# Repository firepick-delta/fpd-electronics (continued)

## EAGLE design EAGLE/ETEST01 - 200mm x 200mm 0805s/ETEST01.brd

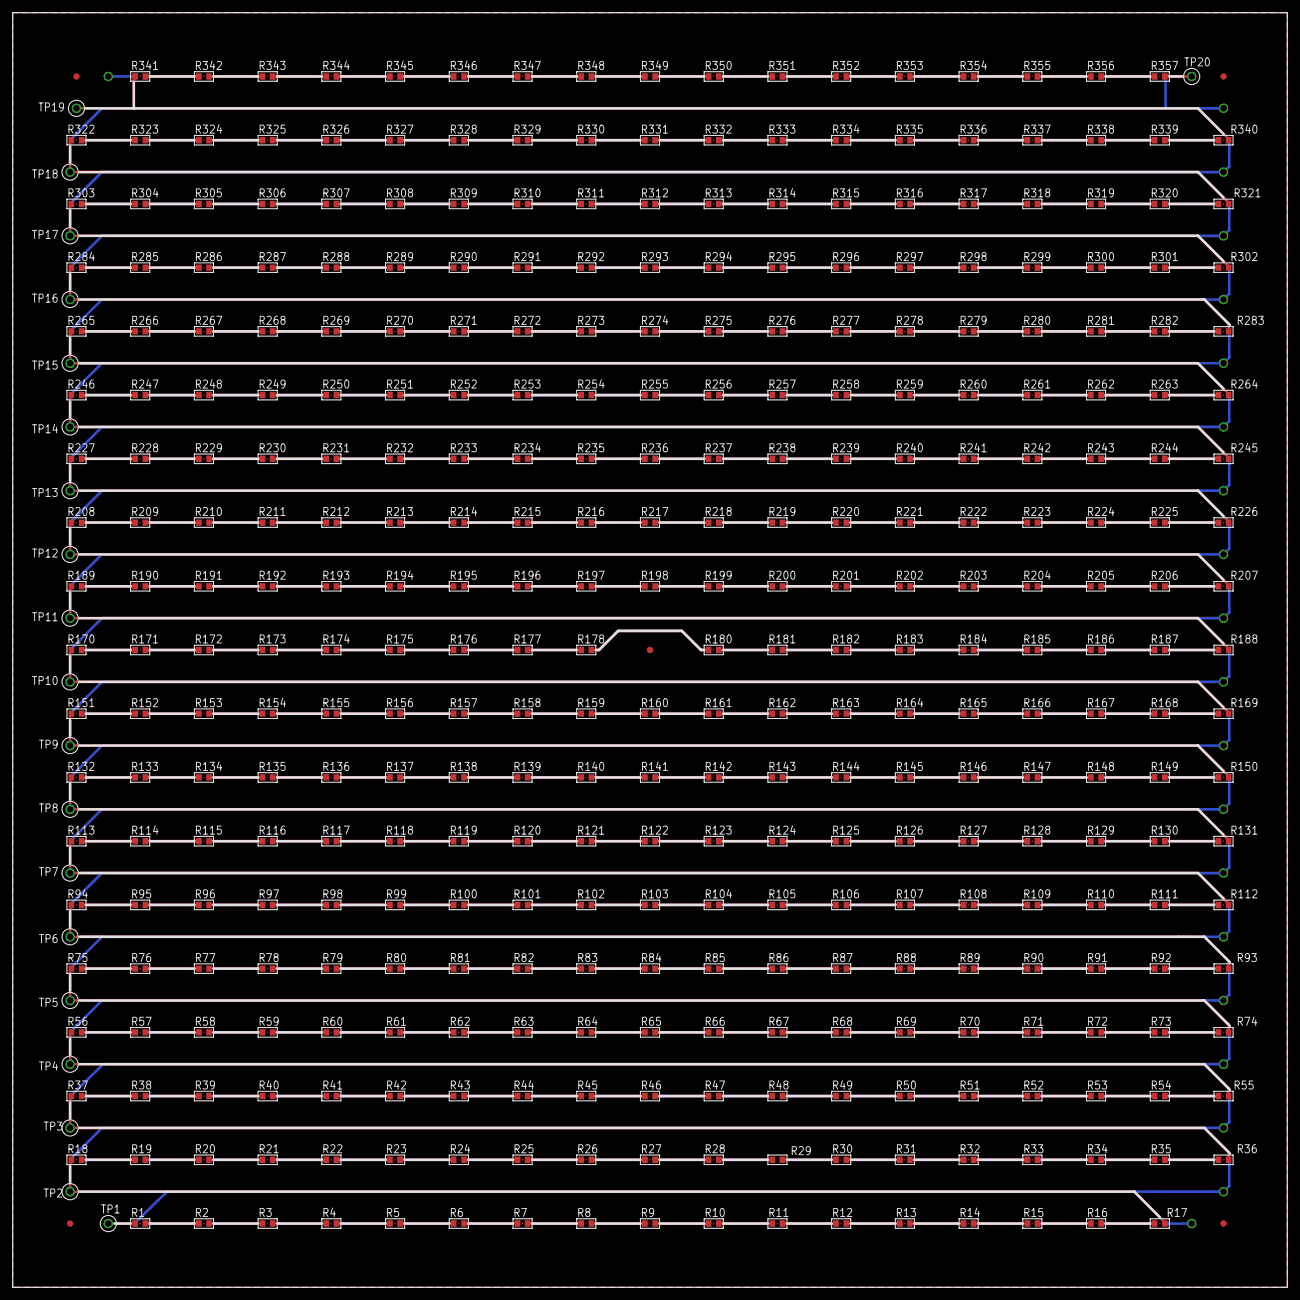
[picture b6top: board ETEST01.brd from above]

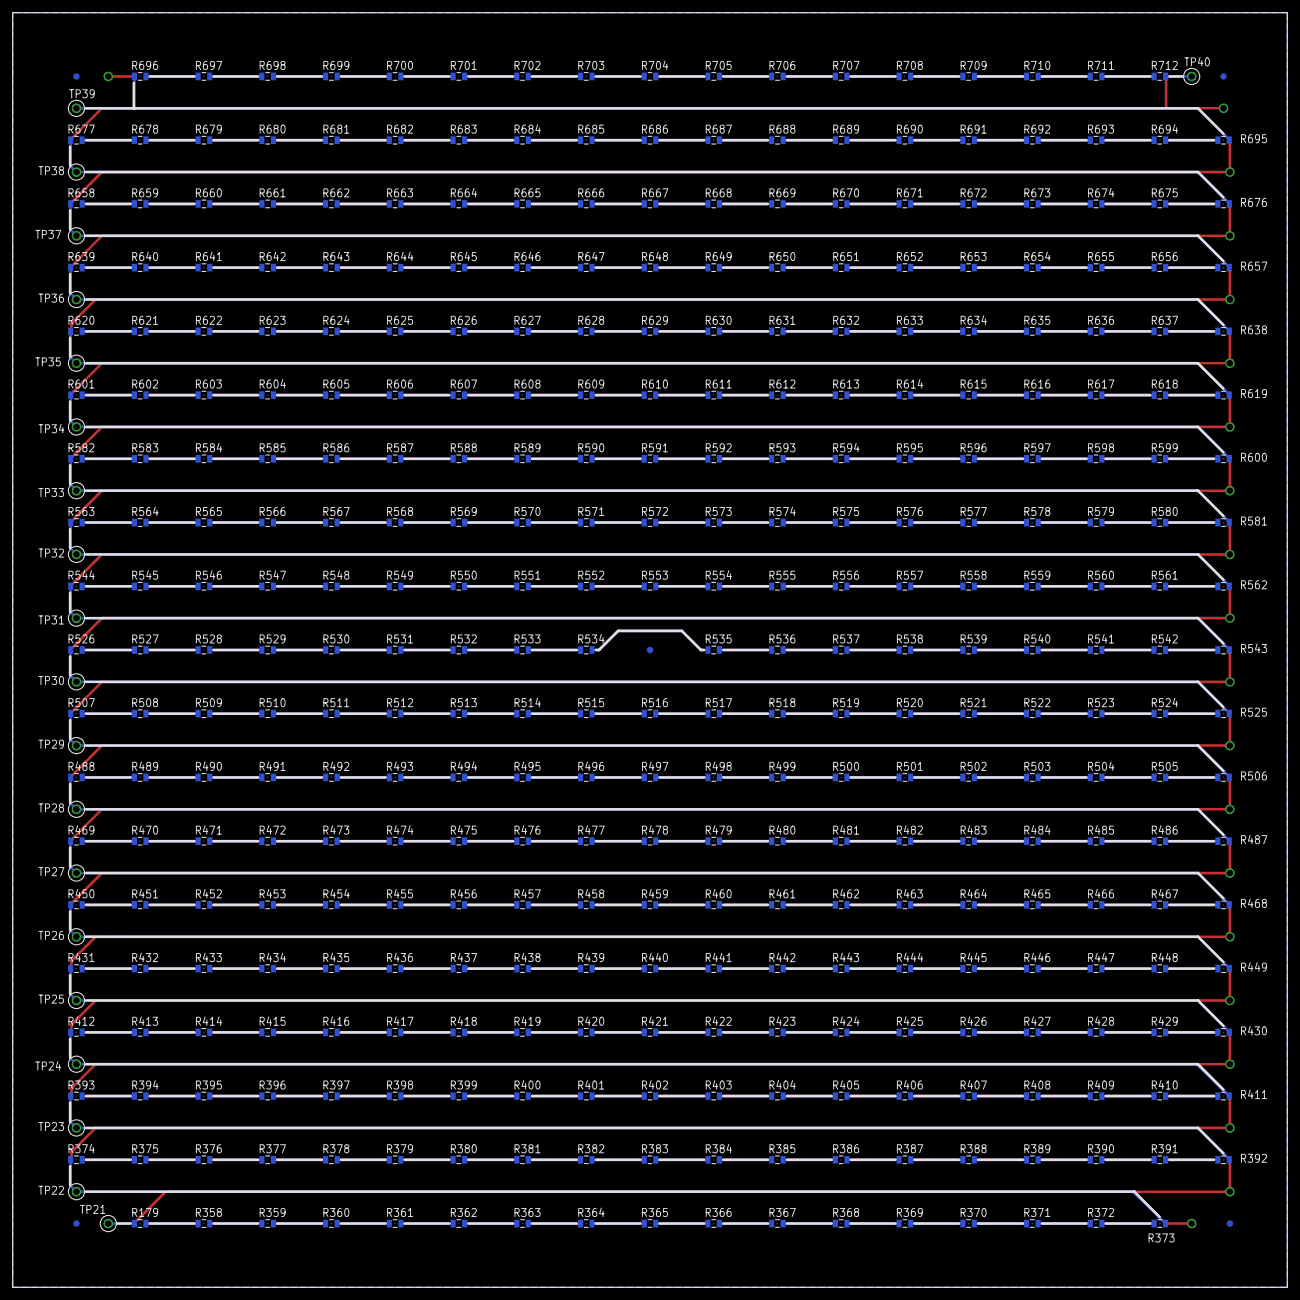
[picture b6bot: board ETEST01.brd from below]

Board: 2 copper layers, 200.0 x 200.0 mm, 762 parts (381 on the bottom side), 714 nets.

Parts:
FID1, FID2, FID3, FID4, FID5, FID6, FID7, FID8, FID9, FID10: FIDUCIAL
R1, R2, R3, R4, R5, R6, R7, R8, R9, R10, R11, R12, R13, R14, R15, R16, R17, R18, R19, R20, R21, R22, R23, R24, R25, R26, R27, R28, R30, R31, R32, R33, R34, R35, R36, R37, R38, R39, R40, R41, R42, R43, R44, R45, R46, R47, R48, R49, R50, R51, R52, R53, R54, R55, R56, R57, R58, R59, R60, R61, R62, R63, R64, R65, R66, R67, R68, R69, R70, R71, R72, R73, R74, R75, R76, R77, R78, R79, R80, R81, R82, R83, R84, R85, R86, R87, R88, R89, R90, R91, R92, R93, R94, R95, R96, R97, R98, R99, R100, R101, R102, R103, R104, R105, R106, R107, R108, R109, R110, R111, R112, R113, R114, R115, R116, R117, R118, R119, R120, R121, R122, R123, R124, R125, R126, R127, R128, R129, R130, R131, R132, R133, R134, R135, R136, R137, R138, R139, R140, R141, R142, R143, R144, R145, R146, R147, R148, R149, R150, R151, R152, R153, R154, R155, R156, R157, R158, R159, R160, R161, R162, R163, R164, R165, R166, R167, R168, R169, R170, R171, R172, R173, R174, R175, R176, R177, R178, R180, R181, R182, R183, R184, R185, R186, R187, R188, R189, R190, R191, R192, R193, R194, R195, R196, R197, R198, R199, R200, R201, R202, R203, R204, R205, R206, R207, R208, R209, R210, R211, R212, R213, R214, R215, R216, R217, R218, R219, R220, R221, R222, R223, R224, R225, R226, R227, R228, R229, R230, R231, R232, R233, R234, R235, R236, R237, R238, R239, R240, R241, R242, R243, R244, R245, R246, R247, R248, R249, R250, R251, R252, R253, R254, R255, R256, R257, R258, R259, R260, R261, R262, R263, R264, R265, R266, R267, R268, R269, R270, R271, R272, R273, R274, R275, R276, R277, R278, R279, R280, R281, R282, R283, R284, R285, R286, R287, R288, R289, R290, R291, R292, R293, R294, R295, R296, R297, R298, R299, R300, R301, R302, R303, R304, R305, R306, R307, R308, R309, R310, R311, R312, R313, R314, R315, R316, R317, R318, R319, R320, R321, R322, R323, R324, R325, R326, R327, R328, R329, R330, R331, R332, R333, R334, R335, R336, R337, R338, R339, R340, R341, R342, R343, R344, R345, R346, R347, R348, R349, R350, R351, R352, R353, R354, R355, R356, R357: TESTPKG-RESISTOR0603; TESTPKG-R0603
R29: CPL-RES-0603-0-0.1W; R0603
R179, R358, R359, R360, R361, R362, R363, R364, R365, R366, R367, R368, R369, R370, R371, R372, R373, R374, R375, R376, R377, R378, R379, R380, R381, R382, R383, R384, R385, R386, R387, R388, R389, R390, R391, R392, R393, R394, R395, R396, R397, R398, R399, R400, R401, R402, R403, R404, R405, R406, R407, R408, R409, R410, R411, R412, R413, R414, R415, R416, R417, R418, R419, R420, R421, R422, R423, R424, R425, R426, R427, R428, R429, R430, R431, R432, R433, R434, R435, R436, R437, R438, R439, R440, R441, R442, R443, R444, R445, R446, R447, R448, R449, R450, R451, R452, R453, R454, R455, R456, R457, R458, R459, R460, R461, R462, R463, R464, R465, R466, R467, R468, R469, R470, R471, R472, R473, R474, R475, R476, R477, R478, R479, R480, R481, R482, R483, R484, R485, R486, R487, R488, R489, R490, R491, R492, R493, R494, R495, R496, R497, R498, R499, R500, R501, R502, R503, R504, R505, R506, R507, R508, R509, R510, R511, R512, R513, R514, R515, R516, R517, R518, R519, R520, R521, R522, R523, R524, R525, R526, R527, R528, R529, R530, R531, R532, R533, R534, R535, R536, R537, R538, R539, R540, R541, R542, R543, R544, R545, R546, R547, R548, R549, R550, R551, R552, R553, R554, R555, R556, R557, R558, R559, R560, R561, R562, R563, R564, R565, R566, R567, R568, R569, R570, R571, R572, R573, R574, R575, R576, R577, R578, R579, R580, R581, R582, R583, R584, R585, R586, R587, R588, R589, R590, R591, R592, R593, R594, R595, R596, R597, R598, R599, R600, R601, R602, R603, R604, R605, R606, R607, R608, R609, R610, R611, R612, R613, R614, R615, R616, R617, R618, R619, R620, R621, R622, R623, R624, R625, R626, R627, R628, R629, R630, R631, R632, R633, R634, R635, R636, R637, R638, R639, R640, R641, R642, R643, R644, R645, R646, R647, R648, R649, R650, R651, R652, R653, R654, R655, R656, R657, R658, R659, R660, R661, R662, R663, R664, R665, R666, R667, R668, R669, R670, R671, R672, R673, R674, R675, R676, R677, R678, R679, R680, R681, R682, R683, R684, R685, R686, R687, R688, R689, R690, R691, R692, R693, R694, R695, R696, R697, R698, R699, R700, R701, R702, R703, R704, R705, R706, R707, R708, R709, R710, R711, R712: TESTPKG-RESISTOR0805; TESTPKG-R0805
TP1, TP2, TP3, TP4, TP5, TP6, TP7, TP8, TP9, TP10, TP11, TP12, TP13, TP14, TP15, TP16, TP17, TP18, TP19, TP20, TP21, TP22, TP23, TP24, TP25, TP26, TP27, TP28, TP29, TP30, TP31, TP32, TP33, TP34, TP35, TP36, TP37, TP38, TP39, TP40: CONN-TESTPOINT; CON-TESTPOINT

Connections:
unnamed: R228.2, R229.1
unnamed: R226.2, R227.1, TP13.1
unnamed: R225.2, R226.1
unnamed: R224.2, R225.1
unnamed: R223.2, R224.1
unnamed: R222.2, R223.1
unnamed: R221.2, R222.1
unnamed: R220.2, R221.1
unnamed: R219.2, R220.1
unnamed: R218.2, R219.1
unnamed: R217.2, R218.1
unnamed: R216.2, R217.1
unnamed: R215.2, R216.1
unnamed: R214.2, R215.1
unnamed: R213.2, R214.1
unnamed: R212.2, R213.1
unnamed: R342.2, R343.1
unnamed: R211.2, R212.1
unnamed: R210.2, R211.1
unnamed: R209.2, R210.1
unnamed: R207.2, R208.1, TP12.1
unnamed: R206.2, R207.1
unnamed: R205.2, R206.1
unnamed: R204.2, R205.1
unnamed: R203.2, R204.1
unnamed: R202.2, R203.1
unnamed: R201.2, R202.1
unnamed: R200.2, R201.1
unnamed: R199.2, R200.1
unnamed: R198.2, R199.1
unnamed: R197.2, R198.1
unnamed: R196.2, R197.1
unnamed: R195.2, R196.1
unnamed: R194.2, R195.1
unnamed: R193.2, R194.1
unnamed: R192.2, R193.1
unnamed: R191.2, R192.1
unnamed: R190.2, R191.1
unnamed: R188.2, R189.1, TP11.1
unnamed: R187.2, R188.1
unnamed: R186.2, R187.1
unnamed: R185.2, R186.1
unnamed: R184.2, R185.1
unnamed: R183.2, R184.1
unnamed: R182.2, R183.1
unnamed: R181.2, R182.1
unnamed: R180.2, R181.1
unnamed: R178.2, R180.1
unnamed: R357.2, TP20.1
unnamed: R177.2, R178.1
unnamed: R176.2, R177.1
unnamed: R175.2, R176.1
unnamed: R174.2, R175.1
unnamed: R173.2, R174.1
unnamed: R172.2, R173.1
unnamed: R171.2, R172.1
unnamed: R169.2, R170.1, TP10.1
unnamed: R168.2, R169.1
unnamed: R167.2, R168.1
unnamed: R166.2, R167.1
unnamed: R165.2, R166.1
unnamed: R164.2, R165.1
unnamed: R163.2, R164.1
unnamed: R162.2, R163.1
unnamed: R161.2, R162.1
unnamed: R160.2, R161.1
unnamed: R159.2, R160.1
unnamed: R158.2, R159.1
unnamed: R157.2, R158.1
unnamed: R156.2, R157.1
unnamed: R155.2, R156.1
unnamed: R154.2, R155.1
unnamed: R153.2, R154.1
unnamed: R152.2, R153.1
unnamed: R150.2, R151.1, TP9.1
unnamed: R149.2, R150.1
unnamed: R148.2, R149.1
unnamed: R147.2, R148.1
unnamed: R146.2, R147.1
unnamed: R145.2, R146.1
unnamed: R144.2, R145.1
unnamed: R143.2, R144.1
unnamed: R142.2, R143.1
unnamed: R141.2, R142.1
unnamed: R140.2, R141.1
unnamed: R139.2, R140.1
unnamed: R138.2, R139.1
unnamed: R137.2, R138.1
unnamed: R136.2, R137.1
unnamed: R135.2, R136.1
unnamed: R134.2, R135.1
unnamed: R133.2, R134.1
unnamed: R131.2, R132.1, TP8.1
unnamed: R130.2, R131.1
unnamed: R129.2, R130.1
unnamed: R128.2, R129.1
unnamed: R127.2, R128.1
unnamed: R126.2, R127.1
unnamed: R125.2, R126.1
unnamed: R124.2, R125.1
unnamed: R123.2, R124.1
unnamed: R122.2, R123.1
unnamed: R121.2, R122.1
unnamed: R120.2, R121.1
unnamed: R119.2, R120.1
unnamed: R118.2, R119.1
unnamed: R117.2, R118.1
unnamed: R116.2, R117.1
unnamed: R115.2, R116.1
unnamed: R114.2, R115.1
unnamed: R112.2, R113.1, TP7.1
unnamed: R111.2, R112.1
unnamed: R110.2, R111.1
unnamed: R109.2, R110.1
unnamed: R108.2, R109.1
unnamed: R107.2, R108.1
unnamed: R106.2, R107.1
unnamed: R105.2, R106.1
unnamed: R104.2, R105.1
unnamed: R103.2, R104.1
unnamed: R102.2, R103.1
unnamed: R101.2, R102.1
unnamed: R100.2, R101.1
unnamed: R99.2, R100.1
unnamed: R98.2, R99.1
unnamed: R97.2, R98.1
unnamed: R96.2, R97.1
unnamed: R95.2, R96.1
unnamed: R93.2, R94.1, TP6.1
unnamed: R92.2, R93.1
unnamed: R91.2, R92.1
unnamed: R90.2, R91.1
unnamed: R89.2, R90.1
unnamed: R88.2, R89.1
unnamed: R87.2, R88.1
unnamed: R86.2, R87.1
unnamed: R85.2, R86.1
unnamed: R84.2, R85.1
unnamed: R83.2, R84.1
unnamed: R82.2, R83.1
unnamed: R81.2, R82.1
unnamed: R80.2, R81.1
unnamed: R79.2, R80.1
unnamed: R78.2, R79.1
unnamed: R77.2, R78.1
unnamed: R76.2, R77.1
unnamed: R75.2, R76.1
unnamed: R73.2, R74.1
unnamed: R72.2, R73.1
unnamed: R71.2, R72.1
unnamed: R70.2, R71.1
unnamed: R69.2, R70.1
unnamed: R68.2, R69.1
unnamed: R67.2, R68.1
unnamed: R66.2, R67.1
unnamed: R65.2, R66.1
unnamed: R64.2, R65.1
unnamed: R63.2, R64.1
unnamed: R62.2, R63.1
unnamed: R61.2, R62.1
unnamed: R60.2, R61.1
unnamed: R59.2, R60.1
unnamed: R58.2, R59.1
unnamed: R57.2, R58.1
unnamed: R56.2, R57.1
unnamed: R54.2, R55.1
unnamed: R53.2, R54.1
unnamed: R52.2, R53.1
unnamed: R51.2, R52.1
unnamed: R50.2, R51.1
unnamed: R49.2, R50.1
unnamed: R48.2, R49.1
unnamed: R47.2, R48.1
unnamed: R46.2, R47.1
unnamed: R45.2, R46.1
unnamed: R44.2, R45.1
unnamed: R43.2, R44.1
unnamed: R42.2, R43.1
unnamed: R41.2, R42.1
unnamed: R40.2, R41.1
unnamed: R39.2, R40.1
unnamed: R38.2, R39.1
unnamed: R37.2, R38.1
unnamed: R35.2, R36.1
unnamed: R34.2, R35.1
unnamed: R33.2, R34.1
unnamed: R32.2, R33.1
unnamed: R31.2, R32.1
unnamed: R30.2, R31.1
unnamed: R29.2, R30.1
unnamed: R28.2, R29.1
unnamed: R27.2, R28.1
unnamed: R26.2, R27.1
unnamed: R25.2, R26.1
unnamed: R24.2, R25.1
unnamed: R23.2, R24.1
unnamed: R22.2, R23.1
unnamed: R21.2, R22.1
unnamed: R20.2, R21.1
unnamed: R19.2, R20.1
unnamed: R18.2, R19.1
unnamed: R16.2, R17.1
unnamed: R15.2, R16.1
unnamed: R14.2, R15.1
unnamed: R13.2, R14.1
unnamed: R12.2, R13.1
unnamed: R11.2, R12.1
unnamed: R10.2, R11.1
unnamed: R9.2, R10.1
unnamed: R8.2, R9.1
unnamed: R7.2, R8.1
unnamed: R6.2, R7.1
unnamed: R5.2, R6.1
unnamed: R4.2, R5.1
unnamed: R3.2, R4.1
unnamed: R2.2, R3.1
unnamed: R229.2, R230.1
unnamed: R343.2, R344.1
unnamed: R344.2, R345.1
unnamed: R345.2, R346.1
unnamed: R346.2, R347.1
unnamed: R347.2, R348.1
unnamed: R348.2, R349.1
unnamed: R349.2, R350.1
unnamed: R350.2, R351.1
unnamed: R351.2, R352.1
unnamed: R352.2, R353.1
unnamed: R353.2, R354.1
unnamed: R354.2, R355.1
unnamed: R355.2, R356.1
unnamed: R356.2, R357.1
unnamed: R74.2, R75.1, TP5.1
unnamed: R324.2, R325.1
unnamed: R325.2, R326.1
unnamed: R326.2, R327.1
unnamed: R327.2, R328.1
unnamed: R328.2, R329.1
unnamed: R329.2, R330.1
unnamed: R330.2, R331.1
unnamed: R331.2, R332.1
unnamed: R332.2, R333.1
unnamed: R333.2, R334.1
unnamed: R334.2, R335.1
unnamed: R335.2, R336.1
unnamed: R336.2, R337.1
unnamed: R337.2, R338.1
unnamed: R338.2, R339.1
unnamed: R339.2, R340.1
unnamed: R340.2, R341.1, TP19.1
unnamed: R323.2, R324.1
unnamed: R306.2, R307.1
unnamed: R305.2, R306.1
unnamed: R307.2, R308.1
unnamed: R308.2, R309.1
unnamed: R309.2, R310.1
unnamed: R310.2, R311.1
unnamed: R311.2, R312.1
unnamed: R312.2, R313.1
unnamed: R313.2, R314.1
unnamed: R314.2, R315.1
unnamed: R315.2, R316.1
unnamed: R316.2, R317.1
unnamed: R317.2, R318.1
unnamed: R318.2, R319.1
unnamed: R319.2, R320.1
unnamed: R320.2, R321.1
unnamed: R321.2, R322.1, TP18.1
unnamed: R304.2, R305.1
unnamed: R285.2, R286.1
unnamed: R280.2, R281.1
unnamed: R281.2, R282.1
unnamed: R282.2, R283.1
unnamed: R273.2, R274.1
unnamed: R274.2, R275.1
unnamed: R275.2, R276.1
unnamed: R276.2, R277.1
unnamed: R277.2, R278.1
unnamed: R278.2, R279.1
unnamed: R279.2, R280.1
unnamed: R268.2, R269.1
unnamed: R269.2, R270.1
unnamed: R270.2, R271.1
unnamed: R271.2, R272.1
unnamed: R272.2, R273.1
unnamed: R267.2, R268.1
unnamed: R283.2, R284.1, TP16.1
unnamed: R286.2, R287.1
unnamed: R287.2, R288.1
unnamed: R288.2, R289.1
unnamed: R289.2, R290.1
unnamed: R290.2, R291.1
unnamed: R291.2, R292.1
unnamed: R292.2, R293.1
unnamed: R293.2, R294.1
unnamed: R294.2, R295.1
unnamed: R295.2, R296.1
unnamed: R296.2, R297.1
unnamed: R297.2, R298.1
unnamed: R298.2, R299.1
unnamed: R299.2, R300.1
unnamed: R300.2, R301.1
unnamed: R301.2, R302.1
unnamed: R302.2, R303.1, TP17.1
unnamed: R266.2, R267.1
unnamed: R264.2, R265.1, TP15.1
unnamed: R263.2, R264.1
unnamed: R262.2, R263.1
unnamed: R261.2, R262.1
unnamed: R260.2, R261.1
unnamed: R259.2, R260.1
unnamed: R258.2, R259.1
unnamed: R257.2, R258.1
unnamed: R256.2, R257.1
unnamed: R255.2, R256.1
unnamed: R254.2, R255.1
unnamed: R253.2, R254.1
unnamed: R252.2, R253.1
unnamed: R251.2, R252.1
unnamed: R250.2, R251.1
unnamed: R249.2, R250.1
unnamed: R248.2, R249.1
unnamed: R247.2, R248.1
unnamed: R245.2, R246.1, TP14.1
unnamed: R244.2, R245.1
unnamed: R243.2, R244.1
unnamed: R242.2, R243.1
unnamed: R241.2, R242.1
unnamed: R240.2, R241.1
unnamed: R239.2, R240.1
unnamed: R238.2, R239.1
unnamed: R237.2, R238.1
unnamed: R236.2, R237.1
unnamed: R235.2, R236.1
unnamed: R234.2, R235.1
unnamed: R233.2, R234.1
unnamed: R232.2, R233.1
unnamed: R231.2, R232.1
unnamed: R230.2, R231.1
unnamed: R1.2, R2.1
unnamed: R94.2, R95.1
unnamed: R113.2, R114.1
unnamed: R132.2, R133.1
unnamed: R151.2, R152.1
unnamed: R170.2, R171.1
unnamed: R189.2, R190.1
unnamed: R208.2, R209.1
unnamed: R227.2, R228.1
unnamed: R246.2, R247.1
unnamed: R265.2, R266.1
unnamed: R284.2, R285.1
unnamed: R303.2, R304.1
unnamed: R322.2, R323.1
unnamed: R341.2, R342.1
unnamed: R55.2, R56.1, TP4.1
unnamed: R36.2, R37.1, TP3.1
unnamed: R17.2, R18.1, TP2.1
unnamed: R1.1, TP1.1
unnamed: R584.2, R585.1
unnamed: R698.2, R699.1
unnamed: R699.2, R700.1
unnamed: R700.2, R701.1
unnamed: R701.2, R702.1
unnamed: R702.2, R703.1
unnamed: R703.2, R704.1
unnamed: R704.2, R705.1
unnamed: R705.2, R706.1
unnamed: R706.2, R707.1
unnamed: R707.2, R708.1
unnamed: R708.2, R709.1
unnamed: R709.2, R710.1
unnamed: R710.2, R711.1
unnamed: R711.2, R712.1
unnamed: R679.2, R680.1
unnamed: R680.2, R681.1
unnamed: R681.2, R682.1
unnamed: R682.2, R683.1
unnamed: R683.2, R684.1
unnamed: R684.2, R685.1
unnamed: R685.2, R686.1
unnamed: R686.2, R687.1
unnamed: R687.2, R688.1
unnamed: R688.2, R689.1
unnamed: R689.2, R690.1
unnamed: R690.2, R691.1
unnamed: R691.2, R692.1
unnamed: R692.2, R693.1
unnamed: R693.2, R694.1
unnamed: R694.2, R695.1
unnamed: R695.2, R696.1, TP39.1
unnamed: R697.2, R698.1
unnamed: R678.2, R679.1
unnamed: R661.2, R662.1
unnamed: R660.2, R661.1
unnamed: R662.2, R663.1
unnamed: R663.2, R664.1
unnamed: R664.2, R665.1
unnamed: R665.2, R666.1
unnamed: R666.2, R667.1
unnamed: R667.2, R668.1
unnamed: R668.2, R669.1
unnamed: R669.2, R670.1
unnamed: R670.2, R671.1
unnamed: R671.2, R672.1
unnamed: R672.2, R673.1
unnamed: R673.2, R674.1
unnamed: R674.2, R675.1
unnamed: R675.2, R676.1
unnamed: R676.2, R677.1, TP38.1
unnamed: R659.2, R660.1
unnamed: R640.2, R641.1
unnamed: R641.2, R642.1
unnamed: R642.2, R643.1
unnamed: R643.2, R644.1
unnamed: R644.2, R645.1
unnamed: R645.2, R646.1
unnamed: R646.2, R647.1
unnamed: R647.2, R648.1
unnamed: R648.2, R649.1
unnamed: R649.2, R650.1
unnamed: R650.2, R651.1
unnamed: R651.2, R652.1
unnamed: R652.2, R653.1
unnamed: R653.2, R654.1
unnamed: R654.2, R655.1
unnamed: R655.2, R656.1
unnamed: R656.2, R657.1
unnamed: R657.2, R658.1, TP37.1
unnamed: R622.2, R623.1
unnamed: R623.2, R624.1
unnamed: R624.2, R625.1
unnamed: R625.2, R626.1
unnamed: R626.2, R627.1
unnamed: R627.2, R628.1
unnamed: R628.2, R629.1
unnamed: R629.2, R630.1
unnamed: R630.2, R631.1
unnamed: R631.2, R632.1
unnamed: R632.2, R633.1
unnamed: R633.2, R634.1
unnamed: R634.2, R635.1
unnamed: R635.2, R636.1
unnamed: R636.2, R637.1
unnamed: R637.2, R638.1
unnamed: R638.2, R639.1, TP36.1
unnamed: R621.2, R622.1
unnamed: R619.2, R620.1, TP35.1
unnamed: R618.2, R619.1
unnamed: R617.2, R618.1
unnamed: R616.2, R617.1
unnamed: R615.2, R616.1
unnamed: R614.2, R615.1
unnamed: R613.2, R614.1
unnamed: R612.2, R613.1
unnamed: R611.2, R612.1
unnamed: R610.2, R611.1
unnamed: R609.2, R610.1
unnamed: R608.2, R609.1
unnamed: R607.2, R608.1
unnamed: R606.2, R607.1
unnamed: R605.2, R606.1
unnamed: R604.2, R605.1
unnamed: R603.2, R604.1
unnamed: R602.2, R603.1
unnamed: R600.2, R601.1, TP34.1
unnamed: R599.2, R600.1
unnamed: R598.2, R599.1
unnamed: R597.2, R598.1
unnamed: R596.2, R597.1
unnamed: R595.2, R596.1
unnamed: R594.2, R595.1
unnamed: R593.2, R594.1
unnamed: R592.2, R593.1
unnamed: R591.2, R592.1
unnamed: R590.2, R591.1
unnamed: R589.2, R590.1
unnamed: R588.2, R589.1
unnamed: R587.2, R588.1
unnamed: R586.2, R587.1
unnamed: R585.2, R586.1
unnamed: R583.2, R584.1
unnamed: R581.2, R582.1, TP33.1
unnamed: R580.2, R581.1
unnamed: R579.2, R580.1
unnamed: R578.2, R579.1
unnamed: R577.2, R578.1
unnamed: R576.2, R577.1
unnamed: R575.2, R576.1
unnamed: R574.2, R575.1
unnamed: R573.2, R574.1
unnamed: R572.2, R573.1
unnamed: R571.2, R572.1
unnamed: R570.2, R571.1
unnamed: R569.2, R570.1
unnamed: R568.2, R569.1
unnamed: R567.2, R568.1
unnamed: R566.2, R567.1
unnamed: R565.2, R566.1
unnamed: R564.2, R565.1
unnamed: R562.2, R563.1, TP32.1
unnamed: R561.2, R562.1
unnamed: R560.2, R561.1
unnamed: R559.2, R560.1
unnamed: R558.2, R559.1
unnamed: R557.2, R558.1
unnamed: R556.2, R557.1
unnamed: R555.2, R556.1
unnamed: R554.2, R555.1
unnamed: R553.2, R554.1
unnamed: R552.2, R553.1
unnamed: R551.2, R552.1
unnamed: R550.2, R551.1
unnamed: R549.2, R550.1
unnamed: R548.2, R549.1
unnamed: R547.2, R548.1
unnamed: R546.2, R547.1
unnamed: R545.2, R546.1
unnamed: R543.2, R544.1, TP31.1
unnamed: R542.2, R543.1
unnamed: R541.2, R542.1
unnamed: R540.2, R541.1
unnamed: R539.2, R540.1
unnamed: R538.2, R539.1
unnamed: R537.2, R538.1
unnamed: R536.2, R537.1
unnamed: R535.2, R536.1
unnamed: R533.2, R534.1
unnamed: R532.2, R533.1
unnamed: R531.2, R532.1
unnamed: R530.2, R531.1
unnamed: R529.2, R530.1
unnamed: R528.2, R529.1
unnamed: R527.2, R528.1
unnamed: R525.2, R526.1, TP30.1
unnamed: R524.2, R525.1
unnamed: R523.2, R524.1
unnamed: R522.2, R523.1
unnamed: R521.2, R522.1
unnamed: R520.2, R521.1
unnamed: R519.2, R520.1
unnamed: R518.2, R519.1
unnamed: R517.2, R518.1
unnamed: R516.2, R517.1
unnamed: R515.2, R516.1
unnamed: R514.2, R515.1
unnamed: R513.2, R514.1
unnamed: R512.2, R513.1
unnamed: R511.2, R512.1
unnamed: R510.2, R511.1
unnamed: R509.2, R510.1
unnamed: R508.2, R509.1
unnamed: R506.2, R507.1, TP29.1
unnamed: R505.2, R506.1
unnamed: R504.2, R505.1
unnamed: R503.2, R504.1
unnamed: R502.2, R503.1
unnamed: R501.2, R502.1
unnamed: R500.2, R501.1
unnamed: R499.2, R500.1
unnamed: R498.2, R499.1
unnamed: R497.2, R498.1
unnamed: R496.2, R497.1
unnamed: R495.2, R496.1
unnamed: R494.2, R495.1
unnamed: R493.2, R494.1
unnamed: R492.2, R493.1
unnamed: R491.2, R492.1
unnamed: R490.2, R491.1
unnamed: R489.2, R490.1
unnamed: R487.2, R488.1, TP28.1
unnamed: R486.2, R487.1
unnamed: R485.2, R486.1
unnamed: R484.2, R485.1
unnamed: R483.2, R484.1
unnamed: R482.2, R483.1
unnamed: R481.2, R482.1
unnamed: R480.2, R481.1
unnamed: R479.2, R480.1
unnamed: R478.2, R479.1
unnamed: R477.2, R478.1
unnamed: R476.2, R477.1
unnamed: R475.2, R476.1
unnamed: R474.2, R475.1
unnamed: R473.2, R474.1
unnamed: R472.2, R473.1
unnamed: R471.2, R472.1
unnamed: R470.2, R471.1
unnamed: R468.2, R469.1, TP27.1
unnamed: R467.2, R468.1
unnamed: R466.2, R467.1
unnamed: R465.2, R466.1
unnamed: R464.2, R465.1
unnamed: R463.2, R464.1
unnamed: R462.2, R463.1
unnamed: R461.2, R462.1
unnamed: R460.2, R461.1
unnamed: R459.2, R460.1
unnamed: R458.2, R459.1
unnamed: R457.2, R458.1
unnamed: R456.2, R457.1
unnamed: R455.2, R456.1
unnamed: R454.2, R455.1
unnamed: R453.2, R454.1
unnamed: R452.2, R453.1
unnamed: R451.2, R452.1
unnamed: R449.2, R450.1, TP26.1
unnamed: R448.2, R449.1
unnamed: R447.2, R448.1
unnamed: R446.2, R447.1
unnamed: R445.2, R446.1
unnamed: R444.2, R445.1
unnamed: R443.2, R444.1
unnamed: R442.2, R443.1
unnamed: R441.2, R442.1
unnamed: R440.2, R441.1
unnamed: R439.2, R440.1
unnamed: R438.2, R439.1
unnamed: R437.2, R438.1
unnamed: R436.2, R437.1
unnamed: R435.2, R436.1
unnamed: R434.2, R435.1
unnamed: R433.2, R434.1
unnamed: R432.2, R433.1
unnamed: R429.2, R430.1
unnamed: R428.2, R429.1
unnamed: R427.2, R428.1
unnamed: R426.2, R427.1
unnamed: R425.2, R426.1
unnamed: R424.2, R425.1
unnamed: R423.2, R424.1
unnamed: R422.2, R423.1
unnamed: R421.2, R422.1
unnamed: R420.2, R421.1
unnamed: R419.2, R420.1
unnamed: R418.2, R419.1
unnamed: R417.2, R418.1
unnamed: R416.2, R417.1
unnamed: R415.2, R416.1
unnamed: R414.2, R415.1
unnamed: R413.2, R414.1
unnamed: R410.2, R411.1
unnamed: R409.2, R410.1
unnamed: R408.2, R409.1
unnamed: R407.2, R408.1
unnamed: R406.2, R407.1
unnamed: R405.2, R406.1
unnamed: R404.2, R405.1
unnamed: R403.2, R404.1
unnamed: R402.2, R403.1
unnamed: R401.2, R402.1
unnamed: R400.2, R401.1
unnamed: R399.2, R400.1
unnamed: R398.2, R399.1
unnamed: R397.2, R398.1
unnamed: R396.2, R397.1
unnamed: R395.2, R396.1
unnamed: R394.2, R395.1
unnamed: R391.2, R392.1
unnamed: R390.2, R391.1
unnamed: R389.2, R390.1
unnamed: R388.2, R389.1
unnamed: R387.2, R388.1
unnamed: R386.2, R387.1
unnamed: R385.2, R386.1
unnamed: R384.2, R385.1
unnamed: R383.2, R384.1
unnamed: R382.2, R383.1
unnamed: R381.2, R382.1
unnamed: R380.2, R381.1
unnamed: R379.2, R380.1
unnamed: R378.2, R379.1
unnamed: R377.2, R378.1
unnamed: R376.2, R377.1
unnamed: R375.2, R376.1
unnamed: R372.2, R373.1
unnamed: R371.2, R372.1
unnamed: R370.2, R371.1
unnamed: R369.2, R370.1
unnamed: R368.2, R369.1
unnamed: R367.2, R368.1
unnamed: R366.2, R367.1
unnamed: R365.2, R366.1
unnamed: R364.2, R365.1
unnamed: R363.2, R364.1
unnamed: R362.2, R363.1
unnamed: R361.2, R362.1
unnamed: R360.2, R361.1
unnamed: R359.2, R360.1
unnamed: R358.2, R359.1
unnamed: R179.2, R358.1
unnamed: R374.2, R375.1
unnamed: R393.2, R394.1
unnamed: R412.2, R413.1
unnamed: R431.2, R432.1
unnamed: R450.2, R451.1
unnamed: R469.2, R470.1
unnamed: R488.2, R489.1
unnamed: R507.2, R508.1
unnamed: R526.2, R527.1
unnamed: R544.2, R545.1
unnamed: R563.2, R564.1
unnamed: R582.2, R583.1
unnamed: R601.2, R602.1
unnamed: R620.2, R621.1
unnamed: R639.2, R640.1
unnamed: R658.2, R659.1
unnamed: R677.2, R678.1
unnamed: R696.2, R697.1
unnamed: R430.2, R431.1, TP25.1
unnamed: R411.2, R412.1, TP24.1
unnamed: R392.2, R393.1, TP23.1
unnamed: R373.2, R374.1, TP22.1
unnamed: R534.2, R535.1
unnamed: R712.2, TP40.1
unnamed: R179.1, TP21.1
